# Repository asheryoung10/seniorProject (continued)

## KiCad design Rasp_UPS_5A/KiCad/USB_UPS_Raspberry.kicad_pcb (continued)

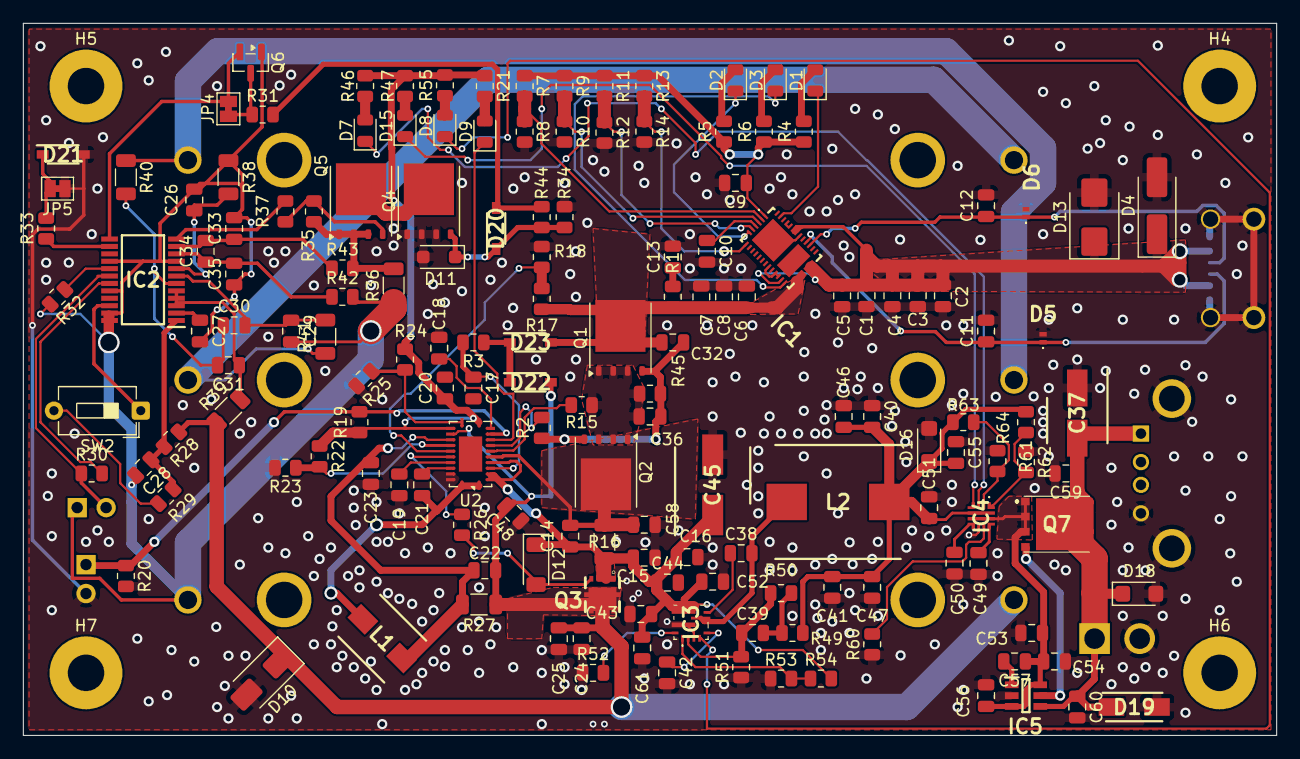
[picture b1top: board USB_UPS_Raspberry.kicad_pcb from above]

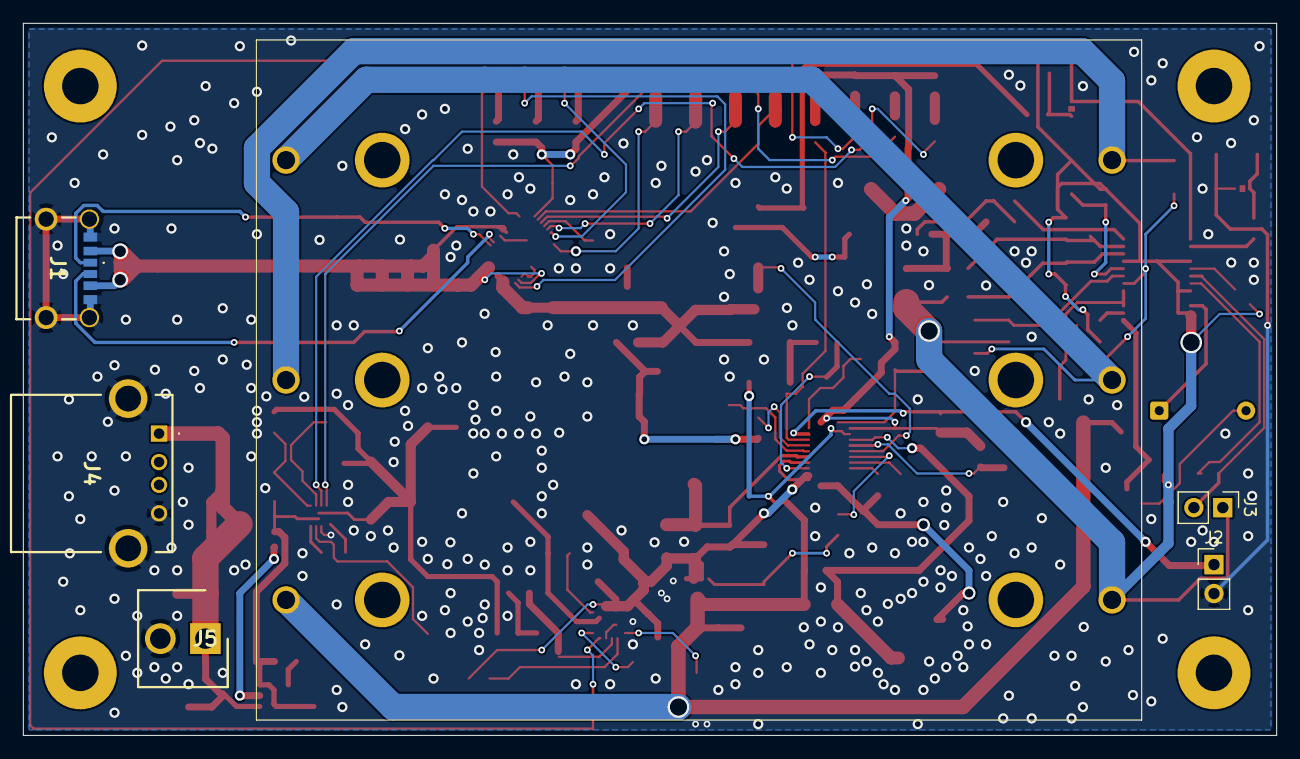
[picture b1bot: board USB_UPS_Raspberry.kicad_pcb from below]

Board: 2 copper layers, 110.0 x 62.5 mm, 169 parts (6 on the bottom side), 90 nets.
